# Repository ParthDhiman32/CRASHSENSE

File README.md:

# CRASHSENSE
Crashsense is a high level embedded sytems project which senses crashes in vehicles like cars trucks and also drones and records crital data of that crash and gives enough data for the crash to be reoncstructed 

# Why did i create this 
i created Crashesense as this is a successor to my older project Dropsense what was dropsense it was simply a embedded system device a PCB inside a hard shell cover which you could drop from any height and it would tell you exactly what height was it droppsed from and also the G-Force with which it impacted the ground

Now this idea grew from a silly project of dropping and analyzing to something bigger i decided to add the best of the best sensors and analyze the data given by then 

Basically Crashsense by it's name you can figure out it is related to something which crashes what crashes?
A lot of things Cars, motorbikes, trucks, drones, ships, and many more vehicles 
Now imagine you could take out something useful from something as negative as a crash from am engineering presepective if Crashsense is intalled in a vehicle from the start if it ever crashes it would give us a lot of DATA....DATA is the most useful thing in engineering which not only tells us how our system behaved but also can be analyzed to fugure out how to make the system behave better and be operate with more accuracy and precision 

Crashsense extracts critical data from a crash like retardation, impact velocity, angle of impact (forward, rear, side, heads on collision) which may be used by engineers to find out how the car crashed and the data may also be analyzed b forensic investigators to collect better evidence. not only all this but if you are making your own custom drone you can install crashsense on it and find out at what exact angle it falls down and how does it fall down and it'll help to pinpoint the point of faliure of the entire system

# HARDWARE & PCB SPECS 

## MICROPROCESSOR
This PCB runs on **ESP32-S3-WROOM-1** operating at speeds of 240Mhz for high frequency data sampling and sensor fusion 

## SENSORS
The main sensors used in this project are 
1. **BMI270** - 6 Axis Inertial Measurement Unit for reading  standard acceleration
2. **ADXL377** - 3 Axis Accelerometer extremely precise readings with massive reading range +-200G
3. **u-blox NEO-M8N** - Additional GPS tracting for pinpointing the location of crash 
4. **DS3231M - precise** timekeeping and timestamping the logged data

## Storage system 
**Push-Push Micro SD-Card Slot** this locks the card firmly inside it's frams and ensures no hinderance with high speed SPI communication 

## Power and Battery Management 
1. **USB-C connector** much better than old micro-usb connectors 
2. **TP4056** for recharing li-ion battries connected in araller for maximum runtime without being connected to external power source
3. **ME6211 3.3V** to step down the 5V input power to stable and low noise 3V3 volts 
4. **Li-ion battries** with JST connector for secure connection 

## Control and Diagnostics #
1. Boot and reset buttons 
2. UART debuggin header (incase USB-C fails to work)

# Schematics

# PCB

# 3D CAD DESIGN

# BOM
| Component | Designator(s) | Qty | LCSC Part # | Manufacturer Part # | Package | Supplier | Total Price (USD) |
|---|---|---|---|---|---|---|---|
| Esp32 S3 | U1 | 1 | C701341 | ESP32-WROOM-32E-N4 | Module | LCSC | $2.50 |
| LowG IMU/GYRO | U2 | 1 | C2828751 | BMI270 | LGA-14 | LCSC | $2.80 |
| High G accelerometer | U3 | 1 | C138128 | ADXL377BCCZ | LFCSP-16 | LCSC | $6.50 |
| Precise RTC | U4 | 1 | C83023 | DS3231MZ+ | SOIC-8 | LCSC | $3.50 |
| 3v3 LDO Regulartor | U5 | 1 | C6186 | AMS1117-3.3 | SOT-223 | LCSC | $0.05 |
| MicroSD Card slot | J1 | 1 | C114227 | MICRO SPI Push-Push | SMD | LCSC | $0.40 |
| GPS Module Header | J2 | 1 | C124375 | Header 1x05 Pin | 2.54mm Pitch | LCSC | $0.05 |
| Power connector | J3 | 1 | C136657 | XT30PW-M | Right_Angle_SMD | LCSC | $0.50 |
| TVS Diode | D1 | 1 | C83307 | SMAJ5.0A | SMA(DO-214AC) | LCSC | $0.08 |
| Schhotkey diode | D2 | 1 | C8598 | SS14 | SMA(DO-214AC) | LCSC | $0.05 |
| I2C Pull up resistors | R1,R2 | 2 | C8598 | 4.7kΩ 1% | 0805 | LCSC | $0.02 |
| ADXL377 Filter Resistors | R3,R4,R5 | 3 | C25804 | 4.7kΩ 1% | 0805 | LCSC | $0.03 |
| ESP32 Boot/EN Pull-ups | R6,R7 | 2 | C17414 | 10kΩ 1% | 0805 | LCSC | $0.02 |
| ADXL377 Filter Capacitors | C1,C2,C3 | 3 | C15849 | 10nF 50V | 0805 | LCSC | $0.06 |
| Bulk Input capacitors | C4,C5 | 2 | C15850 | 10uF 25V | 0805 | LCSC | $0.10 |
| Decoupling Capacitors | C6,C7,C8,C9 | 4 | C14663 | 100nF 50V | 0805 | LCSC | $0.08 |
| RTC Backup Battery Holder | BT1 | 1 | C70377 | CR1220 Holder | SMD | LCSC | $0.15 |
| **Electronics** | Components BOM (LCSC/DigiKey) | 1 Board | $16.89 | $16.89 | MCU, IMUs, RTC, passives, headers |
| **PCB Fabrication** | 2-Layer FR4 PCB (JLCPCB) | 1 Board (of 5) | $2.40 | $2.40 | ~$12.00 total for minimum 5-pc order + economy shipping |
| **Enclosure** | 3D Printed PETG / ABS Filament | ~50g | $1.00 | $1.00 | Based on standard $20/kg spool (tough PETG/ABS) |

### Total Cost Summary

* **Single Unit Build Cost:** **~$20.29 USD**
* **First 5-Board Prototype Run:** **~$98.45 USD** *(1x $20/kg Filament Spool + 5x Component Sets @ $16.89 + 5x PCBs @ $12.00)*

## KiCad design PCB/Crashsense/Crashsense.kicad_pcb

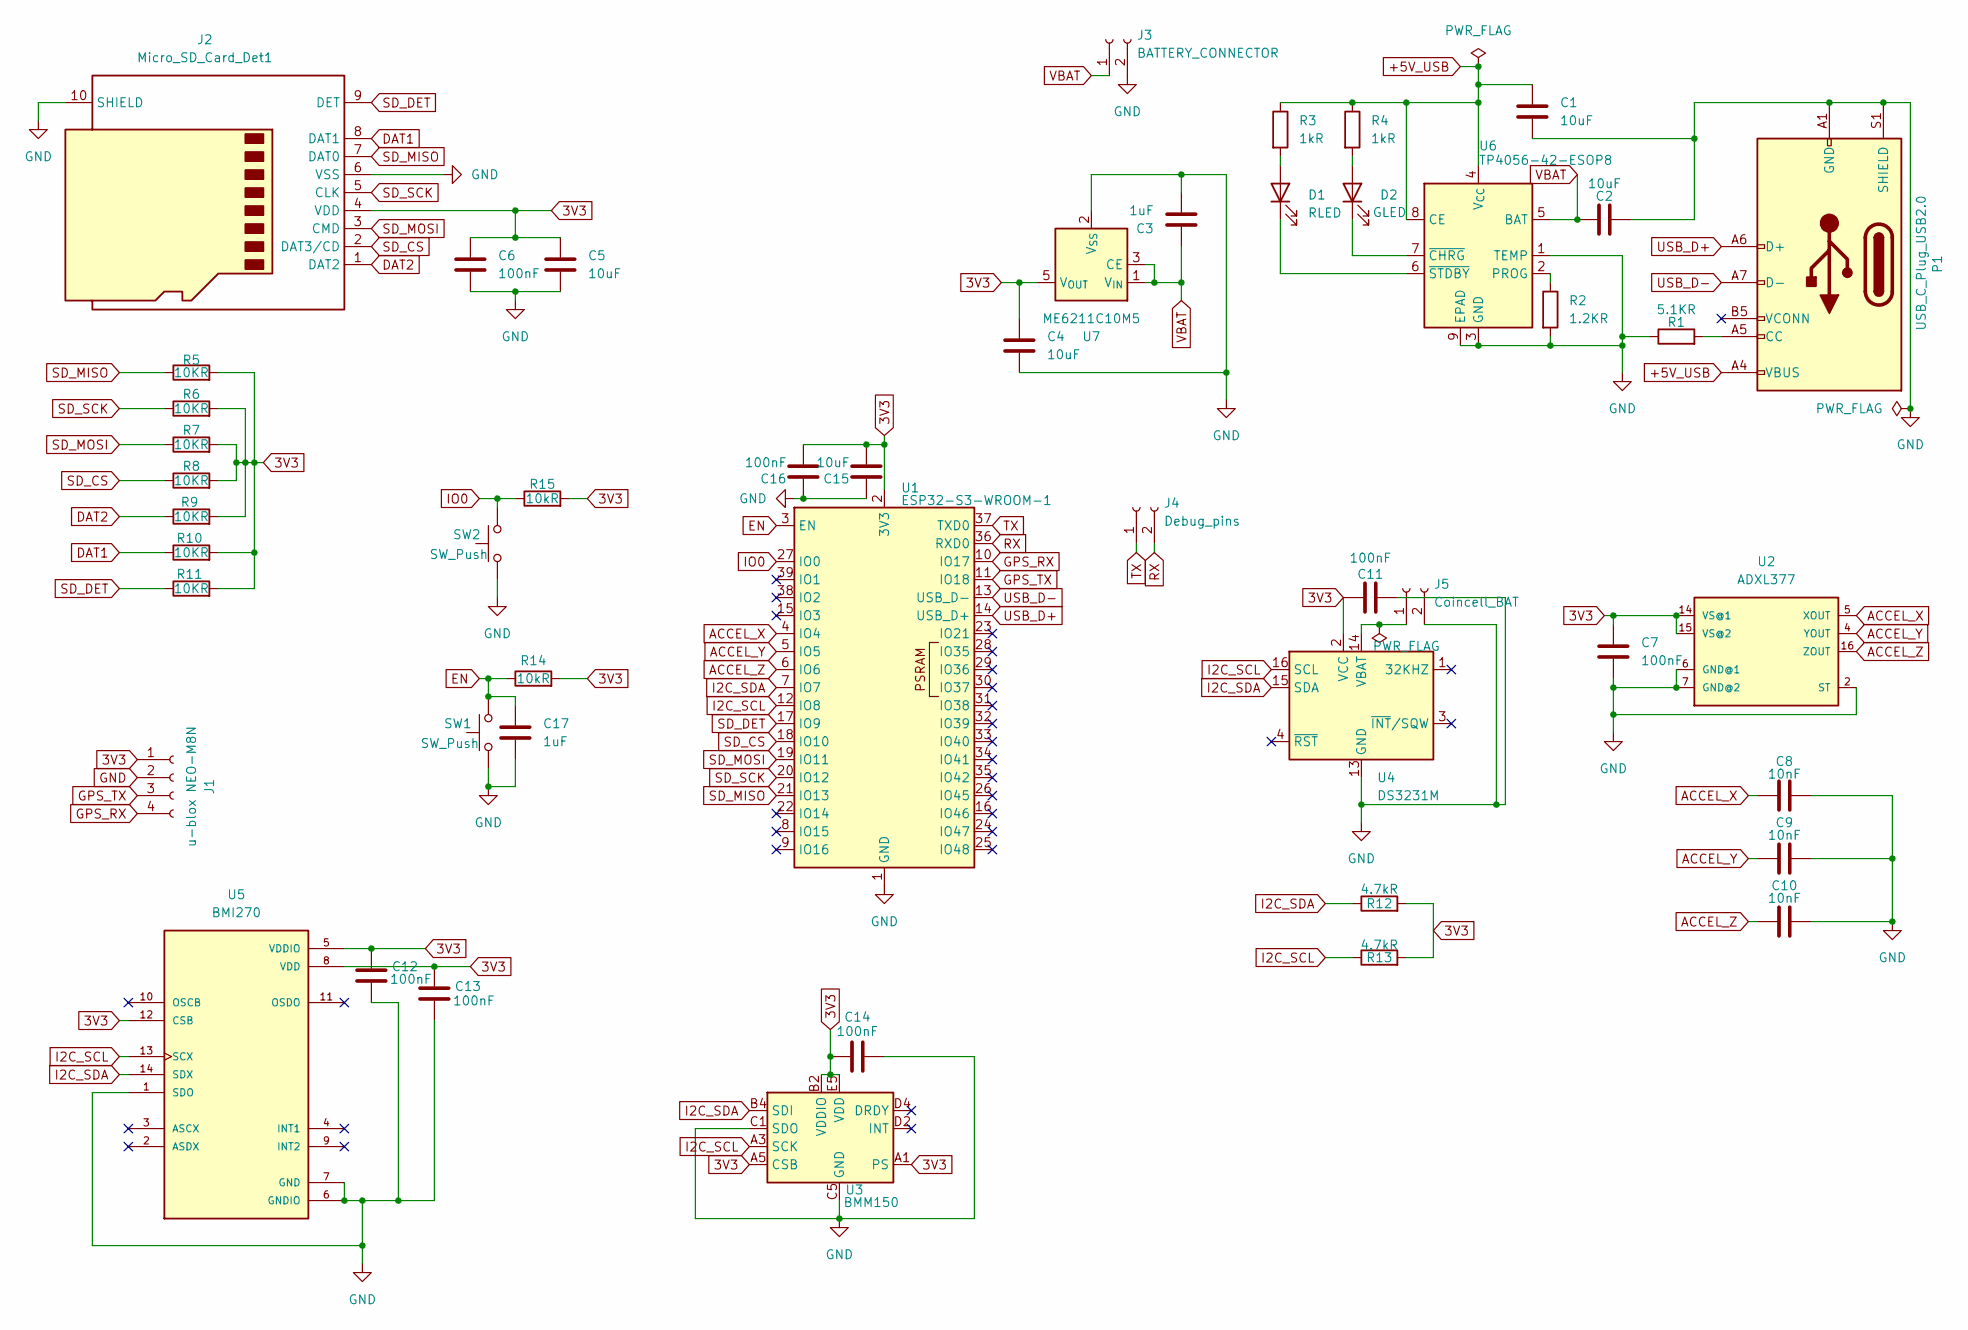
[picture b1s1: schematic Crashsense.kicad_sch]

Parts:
C1, C2, C4, C5, C15: 10uF; C_0805_2012Metric
C3, C17: 1uF; C_0805_2012Metric
C6, C7, C11, C12, C13, C14, C16: 100nF; C_0805_2012Metric
C8, C9, C10: 10nF; C_0805_2012Metric
D1: RLED; LED_0805_2012Metric
D2: GLED; LED_0805_2012Metric
J1: u-blox NEO-M8N; PinHeader_1x04_P2.54mm_Vertical
J2: Micro_SD_Card_Det1; microSD_HC_Hirose_DM3AT-SF-PEJM5
J3: BATTERY_CONNECTOR; JST_PH_B2B-PH-K_1x02_P2.00mm_Vertical
J4: Debug_pins; PinHeader_1x02_P2.54mm_Vertical
J5: Coincell_BAT; JST_PH_B2B-PH-K_1x02_P2.00mm_Vertical
P1: USB_C_Plug_USB2.0; USB_C_Receptacle_HRO_TYPE-C-31-M-12
R1: 5.1KR; R_0805_2012Metric
R2: 1.2KR; R_0805_2012Metric
R3, R4: 1kR; R_0805_2012Metric
R5, R6, R7, R8, R9, R10, R11: 10KR; R_0805_2012Metric
R12, R13: 4.7kR; R_0805_2012Metric
R14, R15: 10kR; R_0805_2012Metric
SW1, SW2: SW_Push; SW_SPST_SKQG_WithStem
U1: ESP32-S3-WROOM-1
U2: ADXL377; LFCSP-16-3X3
U3: BMM150; WLCSP-12_1.56x1.56mm_P0.4mm
U4: DS3231M; SOIC-16W_7.5x10.3mm_P1.27mm
U5: BMI270; XDCR_BMI270
U6: TP4056-42-ESOP8; SOIC-8-1EP_3.9x4.9mm_P1.27mm_EP2.41x3.3mm_ThermalVias
U7: ME6211C10M5; SOT-23-5

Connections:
3V3: C4.1, C5.1, C6.1, C7.1, C11.1, C12.1, C13.1, C14.1, C15.2, C16.2, J1.1, J2.4 (VDD), R5.2, R6.2, R7.2, R8.2, R9.2, R10.2, R11.2, R12.2, R13.2, R14.2, R15.2, U1.2 (3V3), U2.14 (VS@1), U2.15 (VS@2), U3.A1 (PS), U3.A5 (CSB), U3.B2 (VDDIO), U3.E5 (VDD), U4.2 (VCC), U5.5 (VDDIO), U5.8 (VDD), U5.12 (CSB), U7.5 (V_{OUT}); also elsewhere on the board
+5V_USB: C1.1, P1.A4 (VBUS), P1.A9 (VBUS), P1.B4 (VBUS), P1.B9 (VBUS), R3.1, R4.1, U6.4 (V_{CC}), U6.8 (CE)
ACCEL_X: C8.1, U1.4 (IO4), U2.5 (XOUT)
ACCEL_Y: C9.1, U1.5 (IO5), U2.4 (YOUT)
ACCEL_Z: C10.1, U1.6 (IO6), U2.16 (ZOUT)
DAT1: J2.8 (DAT1), R10.1
DAT2: J2.1 (DAT2), R9.1
EN: C17.1, R14.1, SW1.2, U1.3 (EN)
GND: C1.2, C2.2, C3.2, C4.2, C5.2, C6.2, C7.2, C8.2, C9.2, C10.2, C11.2, C12.2, C13.2, C14.2, C15.1, C16.1, C17.2, J2.6 (VSS), J2.10 (SHIELD), J3.2, J5.2, P1.A1 (GND), P1.A12 (GND), P1.B1 (GND), P1.B12 (GND), P1.S1 (SHIELD), R1.1, R2.2, SW1.1, SW2.1, U1.1 (GND), U1.40 (GND), U1.41 (GND), U2.2 (ST), U2.6 (GND@1), U2.7 (GND@2), U3.C1 (SDO), U3.C5 (GND), U3.E1 (GND), U3.E3 (GND), U4.5 (GND), U4.6 (GND), U4.7 (GND), U4.8 (GND), U4.9 (GND), U4.10 (GND), U4.11 (GND), U4.12 (GND), U4.13 (GND), U5.1 (SDO), U5.6 (GNDIO), U5.7 (GND), U6.1 (TEMP), U6.3 (GND), U6.9 (EPAD), U7.2 (V_{SS}); also elsewhere on the board
GPS_RX: J1.4, U1.10 (IO17); also elsewhere on the board
GPS_TX: J1.3, U1.11 (IO18); also elsewhere on the board
I2C_SCL: R13.1, U1.12 (IO8), U3.A3 (SCK), U4.16 (SCL), U5.13 (SCX); also elsewhere on the board
I2C_SDA: R12.1, U1.7 (IO7), U3.B4 (SDI), U4.15 (SDA), U5.14 (SDX); also elsewhere on the board
IO0: R15.1, SW2.2, U1.27 (IO0)
unnamed: D1.2 (A), R3.2
unnamed: D1.1 (K), U6.6 (~STDBY)
unnamed: D2.2 (A), R4.2
unnamed: D2.1 (K), U6.7 (~CHRG)
unnamed 18: J5.1, U4.14 (VBAT); also elsewhere on the board
unnamed: P1.A5 (CC), R1.2
unnamed: R2.1, U6.2 (PROG)
RX: J4.2, U1.36 (RXD0)
SD_CS: J2.2 (DAT3/CD), R8.1, U1.18 (IO10)
SD_DET: J2.9 (DET), R11.1, U1.17 (IO9)
SD_MISO: J2.7 (DAT0), R5.1, U1.21 (IO13)
SD_MOSI: J2.3 (CMD), R7.1, U1.19 (IO11)
SD_SCK: J2.5 (CLK), R6.1, U1.20 (IO12)
TX: J4.1, U1.37 (TXD0)
USB_D+: P1.A6 (D+), U1.14 (USB_D+)
USB_D-: P1.A7 (D-), U1.13 (USB_D-)
VBAT: C2.1, C3.1, J3.1, U6.5 (BAT), U7.1 (V_{IN}), U7.3 (CE)

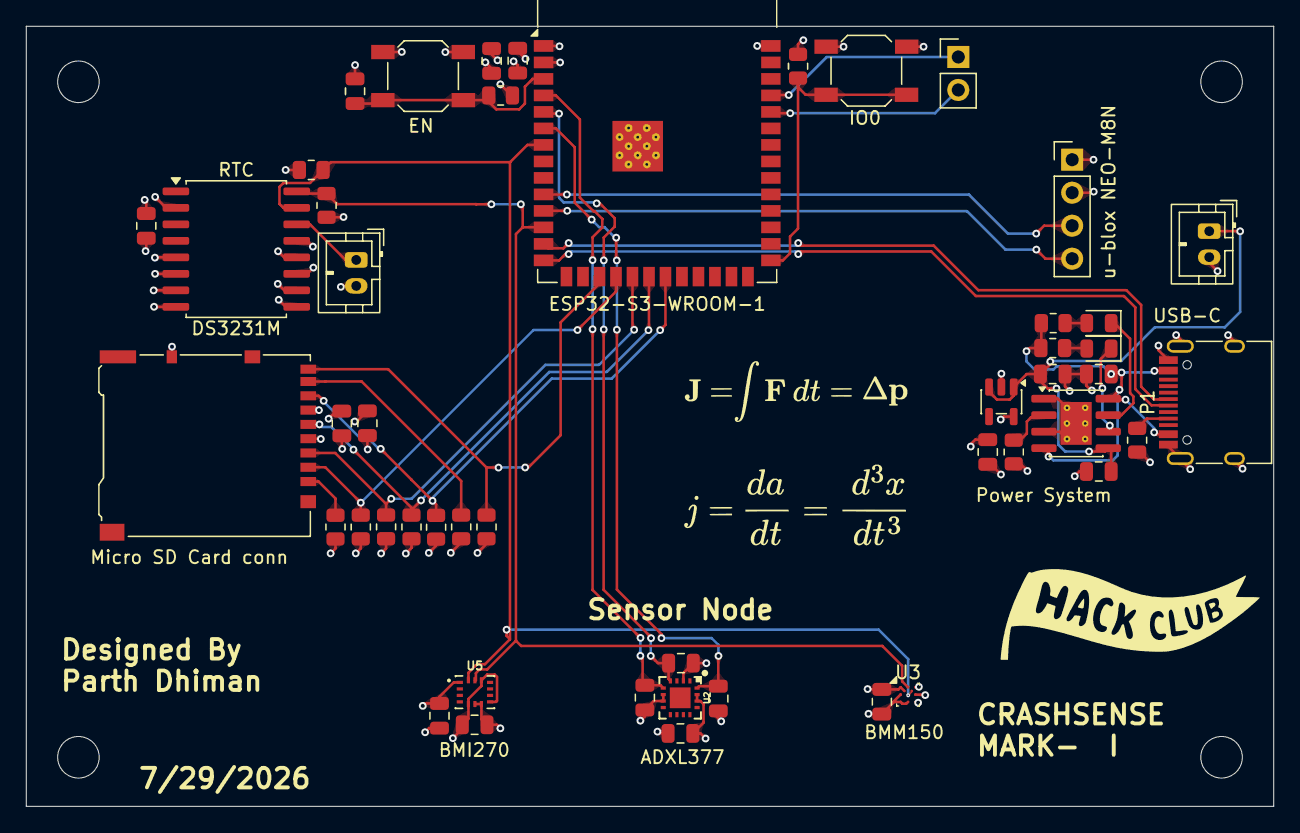
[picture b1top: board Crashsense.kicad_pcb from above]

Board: 4 copper layers, 96.0 x 60.0 mm, 49 parts (0 on the bottom side), 31 nets.

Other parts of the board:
RTC : DS3231M; SOIC-16W_7.5x10.3mm_P1.27mm
u-blox NEO-M8N: u-blox NEO-M8N; PinHeader_1x04_P2.54mm_Vertical

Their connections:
3V3: RTC.2 (VCC), u-blox NEO-M8N.1; also elsewhere on the board
GND: RTC.5 (GND), RTC.6 (GND), RTC.7 (GND), RTC.8 (GND), RTC.9 (GND), RTC.10 (GND), RTC.11 (GND), RTC.12 (GND), RTC.13 (GND), u-blox NEO-M8N.2; also elsewhere on the board
GPS_RX: u-blox NEO-M8N.3; also elsewhere on the board
GPS_TX: u-blox NEO-M8N.4; also elsewhere on the board
I2C_SCL: RTC.16 (SCL); also elsewhere on the board
I2C_SDA: RTC.15 (SDA); also elsewhere on the board
unnamed 18: RTC.14 (VBAT); also elsewhere on the board

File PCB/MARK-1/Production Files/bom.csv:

Designator,Footprint,Quantity,Value,LCSC Part #
,f59ac847-f748-4106-ba1d-d1278d51b1ea,1,,
"C1, C15, C2, C4, C5",0805,5,10uF,
"C10, C8, C9",0805,3,10nF,
"C11, C12, C13, C14, C16, C6, C7",0805,7,100nF,
"C17, C3",0805,2,1uF,
D1,0805,1,RLED,
D2,0805,1,GLED,
J2,microSD_HC_Hirose_DM3AT-SF-PEJM5,1,Micro_SD_Card_Det1,
J3,JST_PH_B2B-PH-K_1x02_P2.00mm_Vertical,1,BATTERY_CONNECTOR,
J4,PinHeader_1x02_P2.54mm_Vertical,1,Debug_pins,
J5,JST_PH_B2B-PH-K_1x02_P2.00mm_Vertical,1,Coincell_BAT,
P1,USB_C_Receptacle_HRO_TYPE-C-31-M-12,1,USB_C_Plug_USB2.0,
R1,0805,1,5.1KR,
"R10, R11, R14, R15, R5, R6, R7, R8, R9",0805,9,10KR,
"R12, R13",0805,2,4.7kR,
R2,0805,1,1.2KR,
"R3, R4",0805,2,1kR,
RTC ,SOIC-16W_7.5x10.3mm_P1.27mm,1,DS3231M,
"SW1, SW2",SW_SPST_SKQG_WithStem,2,SW_Push,
U-BLOX NEO-M8N,PinHeader_1x04_P2.54mm_Vertical,1,u-blox NEO-M8N,
U1,ESP32-S3-WROOM-1,1,ESP32-S3-WROOM-1,
U2,LFCSP-16-3X3,1,ADXL377,
U3,WLCSP-12_1.56x1.56mm_P0.4mm,1,BMM150,
U5,XDCR_BMI270,1,BMI270,
U6,SOIC-8-1EP_3.9x4.9mm_P1.27mm_EP2.41x3.3mm_ThermalVias,1,TP4056-42-ESOP8,
U7,SOT-23-5,1,ME6211C10M5,
